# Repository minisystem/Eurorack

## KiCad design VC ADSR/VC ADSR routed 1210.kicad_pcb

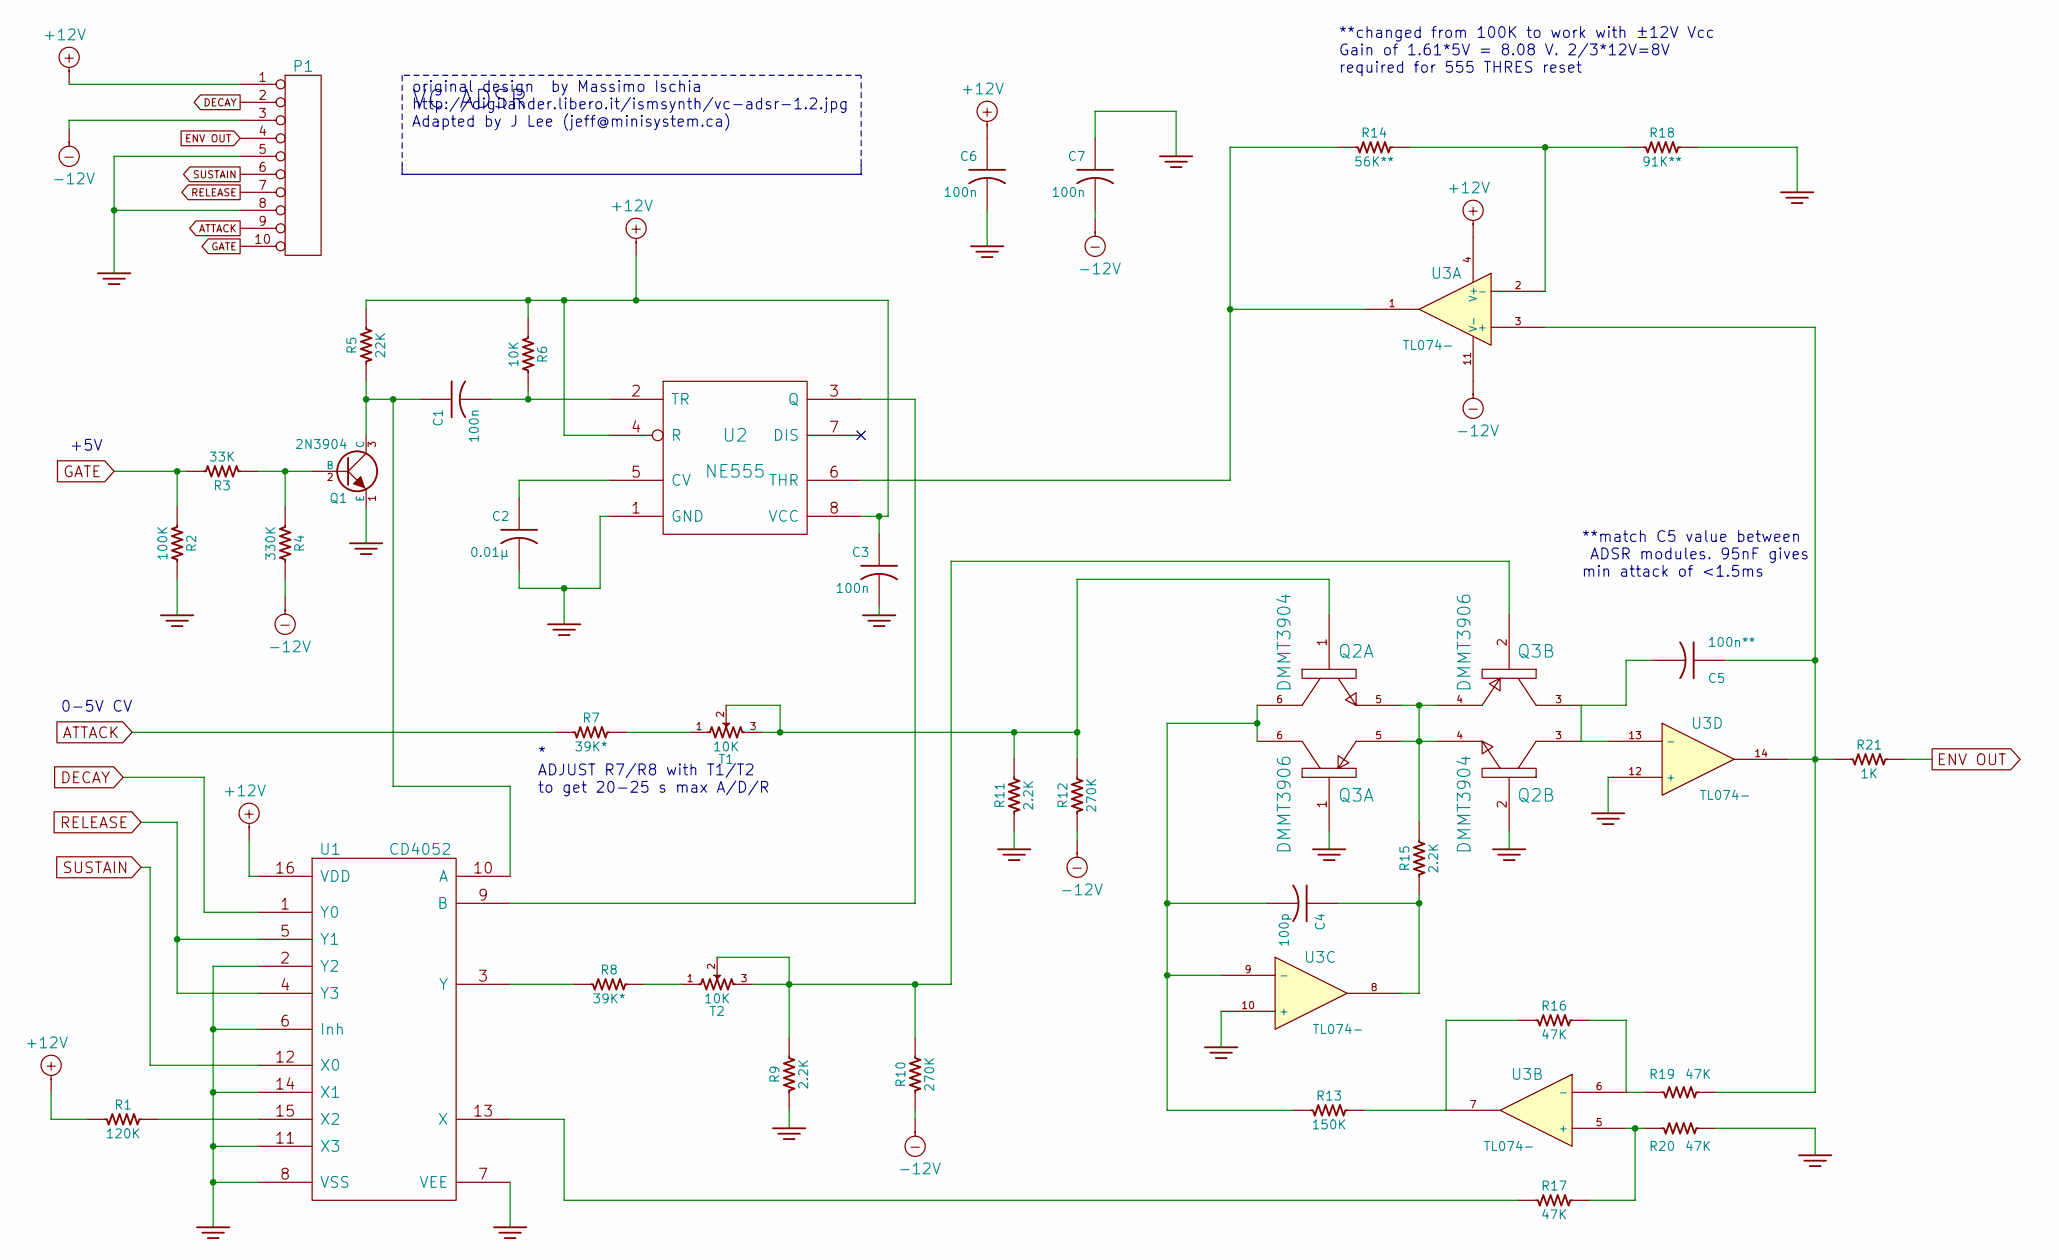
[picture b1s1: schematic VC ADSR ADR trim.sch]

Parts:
C1, C3, C6, C7: 100n
C2: 0.01μ
C4: 100p
C5: 100n**
P1: CONN_10
Q1: 2N3904
Q2: DMMT3904
Q3: DMMT3906
R1: 120K
R2: 100K
R3: 33K
R4: 330K
R5: 22K
R6: 10K
R7, R8: 39K*
R9, R11, R15: 2.2K
R10, R12: 270K
R13: 150K
R14: 56K**
R16, R17, R19, R20: 47K
R18: 91K**
R21: 1K
T1, T2: 10K
U1: CD4052
U2: NE555
U3: TL074-

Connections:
+12V: C3.1, C6.1, P1.1, R1.1, R5.2, R6.1, U1.16 (VDD), U2.4 (R), U2.8 (VCC), U3.4 (V+)
-12V: C7.2, P1.3, R4.2, R10.1, R12.1, U3.11 (V-)
ATTACK: P1.9, R7.1
DECAY: P1.2, U1.1 (Y0)
ENV OUT: P1.4, R21.2
GATE: P1.10, R2.1, R3.2
GND: C2.2, C3.2, C6.2, C7.1, P1.5, P1.8, Q1.1 (E), Q2.2, Q3.1, R2.2, R9.1, R11.1, R18.2, R20.2, U1.2 (Y2), U1.6 (Inh), U1.7 (VEE), U1.8 (VSS), U1.11 (X3), U1.14 (X1), U2.1 (GND), U3.10 (+), U3.12 (+)
unnamed: R14.2, R18.1, U3.2 (-)
unnamed: R14.1, U2.6 (THR), U3.1
unnamed: U1.9 (B), U2.3 (Q)
unnamed: R8.1, U1.3 (Y)
unnamed: Q1.2 (B), R3.1, R4.1
unnamed: C1.1, Q1.3 (C), R5.1, U1.10 (A)
unnamed: C2.1, U2.5 (CV)
unnamed: C1.2, R6.2, U2.2 (TR)
unnamed: Q2.4, Q2.5, Q3.4, Q3.5, R15.2
unnamed: C4.2, Q2.6, Q3.6, R13.1, U3.9 (-)
unnamed: C4.1, R15.1, U3.8
unnamed: R16.2, R19.1, U3.6 (-)
unnamed: R17.1, U1.13 (X)
unnamed: R13.2, R16.1, U3.7
unnamed: C5.2, Q2.3, Q3.3, U3.13 (-)
unnamed: C5.1, R19.2, R21.1, U3.3 (+), U3.14
unnamed: R1.2, U1.15 (X2)
unnamed: R17.2, R20.1, U3.5 (+)
RELEASE: P1.7, U1.4 (Y3), U1.5 (Y1)
SUSTAIN: P1.6, U1.12 (X0)

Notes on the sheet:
**changed from 100K to work with ±12V Vcc Gain of 1.61*5V = 8.08 V. 2/3*12V=8V required for 555 THRES reset
* ADJUST R7/R8 with T1/T2 to get 20-25 s max A/D/R
**match C5 value between ADSR modules. 95nF gives min attack of <1.5ms
0-5V CV
+5V
VC ADSR
original design by Massimo Ischia http://digilander.libero.it/ismsynth/vc-adsr-1.2.jpg Adapted by J Lee (jeff@minisystem.ca)

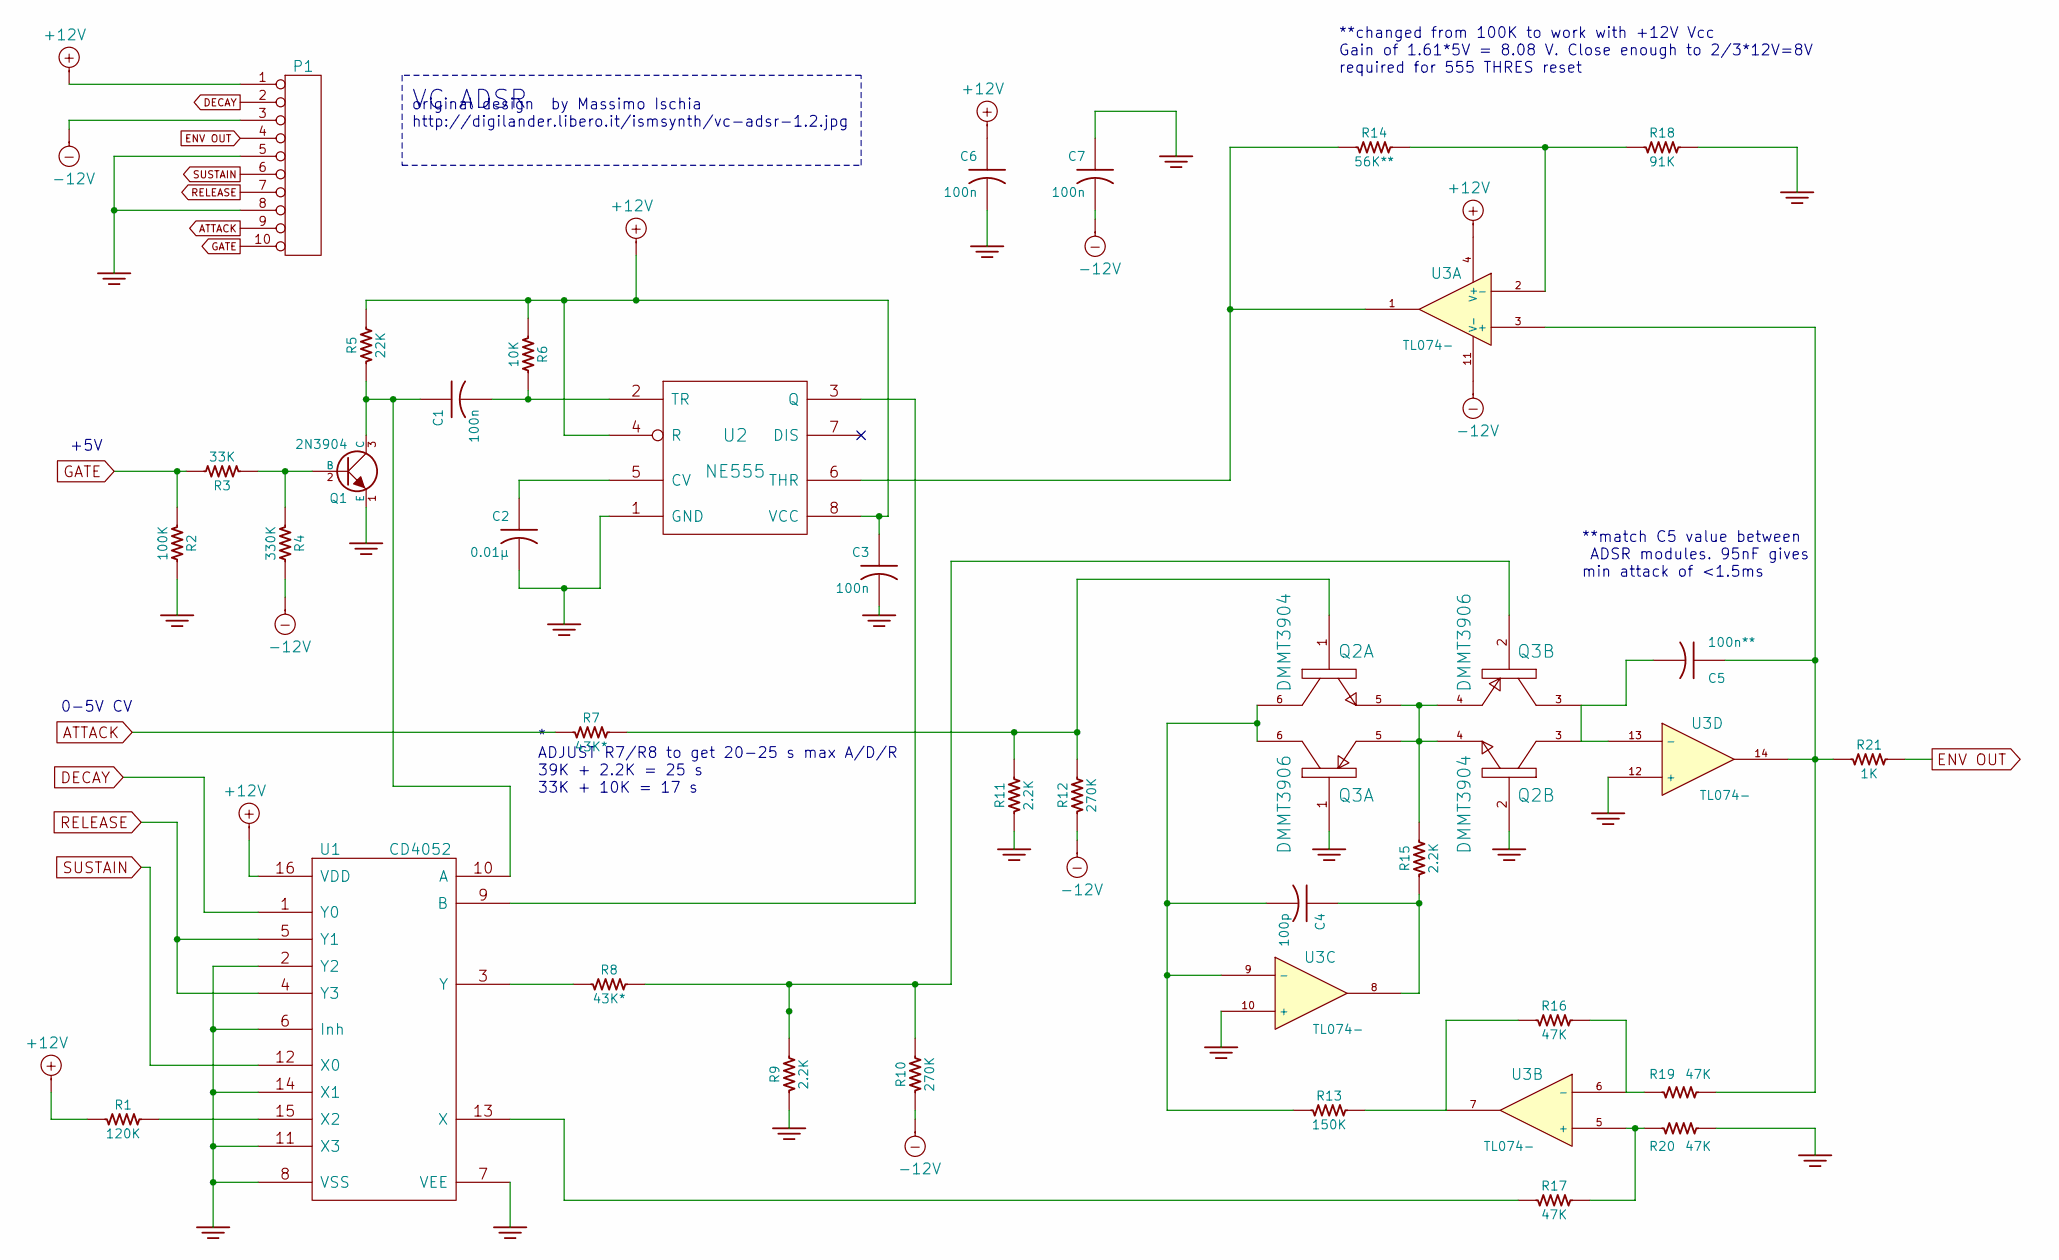
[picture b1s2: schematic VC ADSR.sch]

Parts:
C1, C3, C6, C7: 100n
C2: 0.01μ
C4: 100p
C5: 100n**
P1: CONN_10
Q1: 2N3904
Q2: DMMT3904
Q3: DMMT3906
R1: 120K
R2: 100K
R3: 33K
R4: 330K
R5: 22K
R6: 10K
R7, R8: 43K*
R9, R11, R15: 2.2K
R10, R12: 270K
R13: 150K
R14: 56K**
R16, R17, R19, R20: 47K
R18: 91K
R21: 1K
U1: CD4052
U2: NE555
U3: TL074-

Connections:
+12V: C3.1, C6.1, P1.1, R1.1, R5.2, R6.1, U1.16 (VDD), U2.4 (R), U2.8 (VCC), U3.4 (V+)
-12V: C7.2, P1.3, R4.2, R10.1, R12.1, U3.11 (V-)
ATTACK: P1.9, R7.1
DECAY: P1.2, U1.1 (Y0)
ENV OUT: P1.4, R21.2
GATE: P1.10, R2.1, R3.2
GND: C2.2, C3.2, C6.2, C7.1, P1.5, P1.8, Q1.1 (E), Q2.2, Q3.1, R2.2, R9.1, R11.1, R18.2, R20.2, U1.2 (Y2), U1.6 (Inh), U1.7 (VEE), U1.8 (VSS), U1.11 (X3), U1.14 (X1), U2.1 (GND), U3.10 (+), U3.12 (+)
unnamed: R14.2, R18.1, U3.2 (-)
unnamed: R14.1, U2.6 (THR), U3.1
unnamed: U1.9 (B), U2.3 (Q)
unnamed: R8.1, U1.3 (Y)
unnamed: Q1.2 (B), R3.1, R4.1
unnamed: C1.1, Q1.3 (C), R5.1, U1.10 (A)
unnamed: C2.1, U2.5 (CV)
unnamed: C1.2, R6.2, U2.2 (TR)
unnamed: Q2.4, Q2.5, Q3.4, Q3.5, R15.2
unnamed: C4.2, Q2.6, Q3.6, R13.1, U3.9 (-)
unnamed: C4.1, R15.1, U3.8
unnamed: R16.2, R19.1, U3.6 (-)
unnamed: R17.1, U1.13 (X)
unnamed: R13.2, R16.1, U3.7
unnamed: C5.2, Q2.3, Q3.3, U3.13 (-)
unnamed: C5.1, R19.2, R21.1, U3.3 (+), U3.14
unnamed: R1.2, U1.15 (X2)
unnamed: R17.2, R20.1, U3.5 (+)
RELEASE: P1.7, U1.4 (Y3), U1.5 (Y1)
SUSTAIN: P1.6, U1.12 (X0)

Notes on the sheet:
**changed from 100K to work with +12V Vcc Gain of 1.61*5V = 8.08 V. Close enough to 2/3*12V=8V required for 555 THRES reset
* ADJUST R7/R8 to get 20-25 s max A/D/R 39K + 2.2K = 25 s 33K + 10K = 17 s
**match C5 value between ADSR modules. 95nF gives min attack of <1.5ms
0-5V CV
+5V
VC ADSR
original design by Massimo Ischia http://digilander.libero.it/ismsynth/vc-adsr-1.2.jpg

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
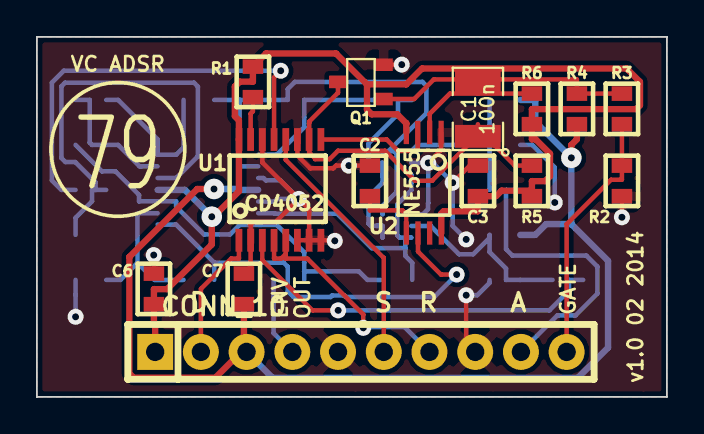
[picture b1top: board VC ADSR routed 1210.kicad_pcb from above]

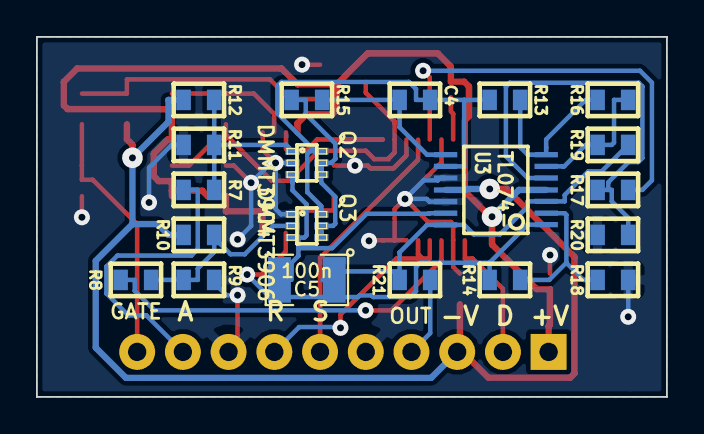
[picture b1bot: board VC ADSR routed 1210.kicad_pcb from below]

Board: 2 copper layers, 35.0 x 20.0 mm, 35 parts (20 on the bottom side), 29 nets.

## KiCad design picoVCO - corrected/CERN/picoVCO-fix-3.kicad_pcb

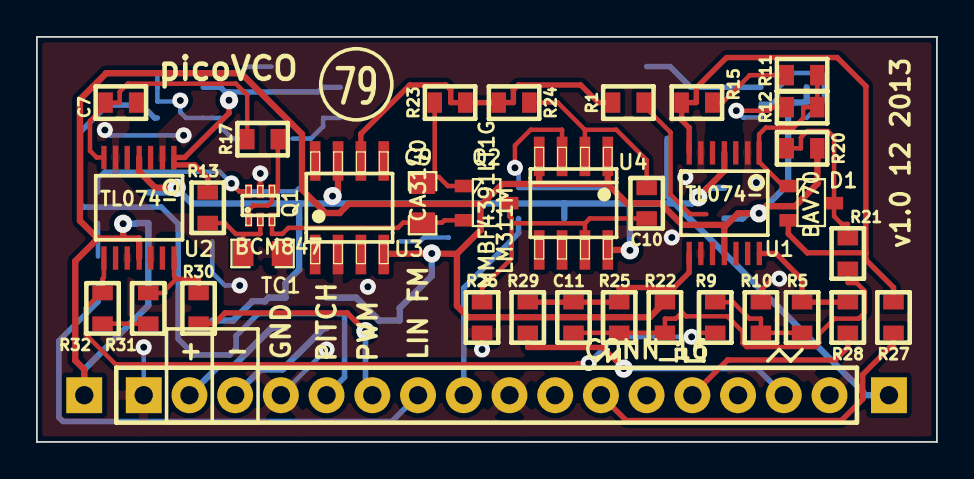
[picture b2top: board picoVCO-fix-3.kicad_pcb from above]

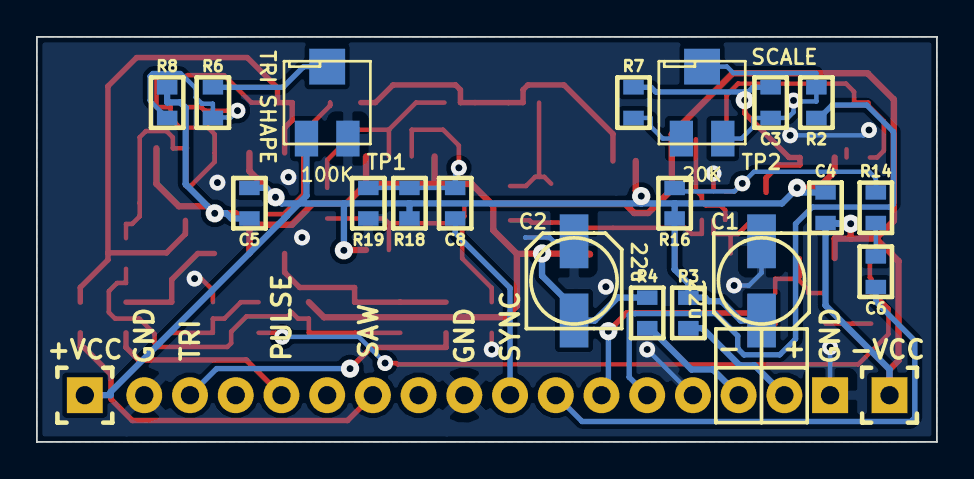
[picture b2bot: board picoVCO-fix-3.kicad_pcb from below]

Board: 2 copper layers, 50.0 x 22.5 mm, 56 parts (21 on the bottom side), 39 nets.

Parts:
C1, C2: 22u; rcl-153CLV-0505
C3, C7, C8, C11: 100p; SM0603-JRL
C4, C5: 100n; SM0603-JRL
C6: 2.2n; SM0603-JRL
C9: 2.2n 1%; SM0805-HAND
C10: 18p; SM0603-JRL
D1: BAV70; SOT23
JP1: CONN_16; SIL-16
JP2, JP3: CONN_1; SIL-1
Q1: BCM847; -SOT363_PHILIPS
Q2: MMBF4391LT1G; SOT23
R1, R9, R17, R19: 10K; SM0603-JRL
R2, R30, R31, R32: 100K; SM0603-JRL
R3, R4: 10; SM0603-JRL
R5, R6, R14: 1M; SM0603-JRL
R7: 91K; SM0603-JRL
R8, R10, R12, R13, R15, R22: 56K; SM0603-JRL
R11: 39K; SM0603-JRL
R16: 1.5M; SM0603-JRL
R18: 20K; SM0603-JRL
R20, R21, R24: 15K; SM0603-JRL
R23: 680; SM0603-JRL
R25: 33K; SM0603-JRL
R26: 3.3K; SM0603-JRL
R27, R28, R29: 1K; SM0603-JRL
TC1: 1K 3300ppm/K; SM0805-HAND
TP1: 100K; 43A
TP2: 20K; 43A
U1, U2: TL074-; TSSOP14
U3: CA3140; SOIC-8-JRL
U4: LM311M; SOIC-8-JRL

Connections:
+15V: C1.1, C4.1, C5.1, JP2.1, R3.2, R16.2, R18.2, TP1.1, U1.4, U2.4, U3.7, U4.8
+15V_PWR: JP1.2, R3.1
-15V: C2.2, C4.2, C5.2, JP3.1, R4.2, R8.1, R20.1, R22.1, U1.11, U2.11, U3.4, U4.1, U4.4
-15V_PWR: JP1.3, R4.1
/RAMP: R1.1, R23.2, R24.2, U3.6
/SCALE: C3.1, R7.2, R13.1, U2.1
/TRI_SHAPE: R6.1, TP1.2
GND_PWR: C1.2, C2.1, JP1.1, JP1.4, JP1.9, JP1.16, Q1.5, R10.2, R19.1, R26.1, TC1.1, TP1.3, U1.3, U1.5, U1.10, U2.3, U2.5, U2.10, U2.12, U3.3
LINEAR_FM: C6.2, JP1.7
unnamed: C3.2, R2.2, TP2.2, TP2.3, U2.2
unnamed: C6.1, R14.1
unnamed: C7.1, Q1.6, R14.2, R16.1, U2.6
unnamed: C7.2, R17.1, U2.7
unnamed: C8.2, R18.1, R19.2, U4.3
unnamed: C9.1, Q1.3, Q2.2, U3.2
unnamed: C9.2, Q2.1, R23.1
unnamed: C10.1, R24.1, U4.2
unnamed: C10.2, Q2.3, R26.2, U4.7
unnamed: C11.1, R21.2, R22.2, R25.1, U1.9
unnamed: D1.1, R11.2, R12.1, U1.1
unnamed: D1.3, R20.2, R21.1
unnamed: Q1.1, Q1.4, R17.2
unnamed: Q1.2, R13.2, TC1.2
unnamed: R1.2, R6.2, R8.2, R11.1, U1.2
unnamed: R7.1, TP2.1
unnamed: R5.2, R9.1, R10.1, U1.12
unnamed: R12.2, R15.1, U1.6
unnamed: R30.2, R31.1, U2.14
unnamed: R31.2, R32.1, U2.9
PITCH_CV: JP1.5, R2.1
PULSE: R5.1, R28.2, U1.14
PULSE_1K: JP1.13, R28.1
PWM_CV: JP1.6, R30.1, U2.13
PWM_SUM: R9.2, R32.2, U2.8
SAW: D1.2, R15.2, R27.2, U1.7, U1.13
SAW_1K: JP1.11, R27.1
SYNC: C8.1, JP1.8
TRI: C11.2, R25.2, R29.2, U1.8
TRI_1K: JP1.15, R29.1
